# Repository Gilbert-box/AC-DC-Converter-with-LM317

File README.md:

# AC-DC Converter with LM317

This is a AC-DC Converter with LM317 voltage regulator IC.  
It converts an AC input into a stable adjustable or fixed 5V DC output using a full-wave bridge rectifier, filter capacitors, and LM317 regulator.

---

## Features

- Input: AC 12–15V (via transformer secondary)
- Output: 1.25V – 12V DC (adjustable) or 5V Fixed 
  *(depends on input voltage and load conditions)*
- Maximum Output Current: 1A (need to add heatsink)
- Built-in fuse protection on AC input

---

## How It Works

1. AC to DC Conversion
   The input AC voltage passes through a **fuse (F1)** for protection.  
   The **bridge rectifier (D1–D4)** converts AC to DC signal.

2. Input Filter 
   Two decoupling capacitors:
   - Polarized Capacitor 1000µF smooths the rectified DC.  
   - Non Polarized 100nF filter high-frequency noise input.

4. Voltage Regulation (LM317)  
   The LM317 regulates the voltage according to the equation:  

5. Output Filter
   Two decoupling capacitors:
   - Polarized Capacitor 1000µF smooths the regulator output.  
   - Non Polarized 100nF filter high-frequency noise.
    
7. Load Output 
   The regulated DC voltage is available at J2 connector pins.

---

## Design Notes

- Use a **12–18V AC transformer** capable of at least **1A output current**.  
- The LM317 requires a **heatsink** for continuous load operation.  
- Output voltage ripple depends on **C1** and load current — for lower ripple, increase C1.  
- Always ensure correct **polarity** before connecting your load.

---

## Applications

- Bench/lab adjustable DC power source  
- Battery charging experiments  
- Testing and calibration of small circuits  
- Educational demonstration of linear voltage regulation

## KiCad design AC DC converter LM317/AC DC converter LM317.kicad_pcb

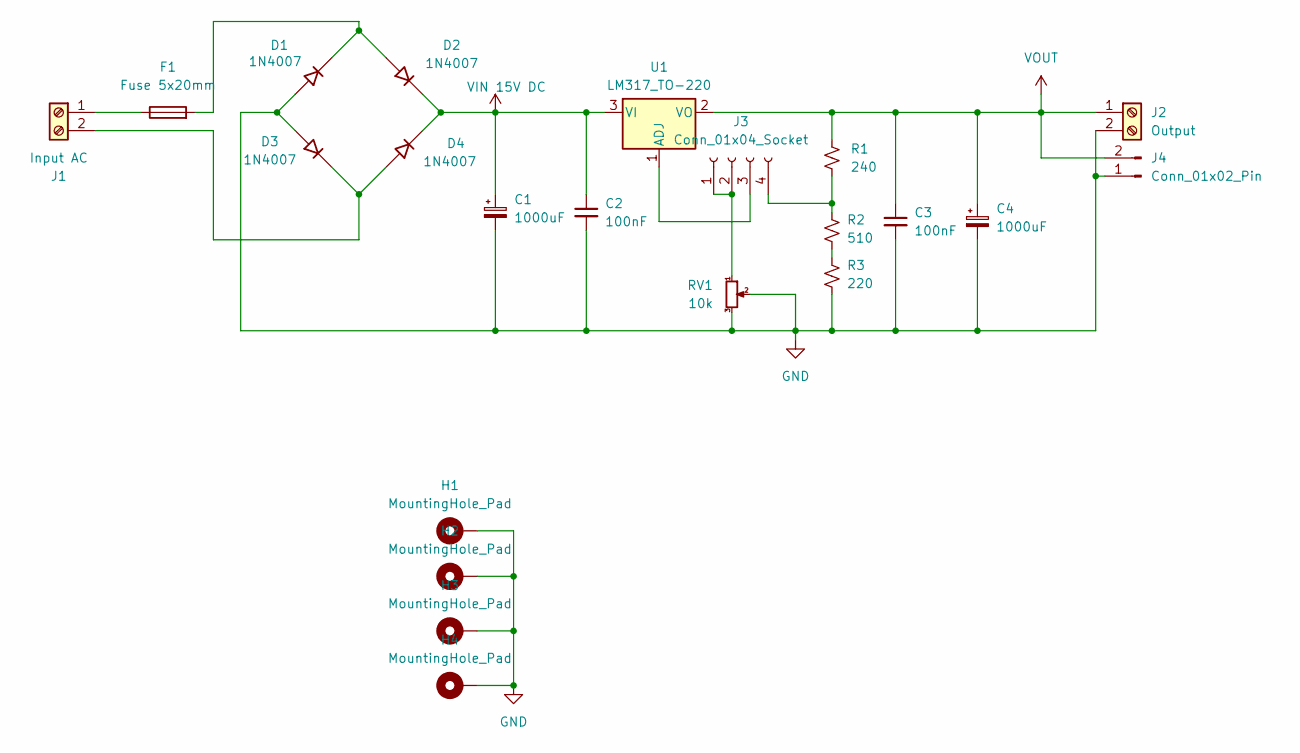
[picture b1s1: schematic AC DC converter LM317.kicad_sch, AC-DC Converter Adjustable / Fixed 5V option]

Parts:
C1, C4: 1000uF; CP_Radial_D10.0mm_P5.00mm
C2, C3: 100nF; C_Rect_L7.0mm_W2.5mm_P5.00mm
D1, D2, D3, D4: 1N4007; D_DO-41_SOD81_P10.16mm_Horizontal
F1: Fuse 5x20mm; Fuseholder_Cylinder-5x20mm_Stelvio-Kontek_PTF78_Horizontal_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
H1, H2, H3, H4: MountingHole_Pad; MountingHole_3.2mm_M3_Pad
J1: Input AC; TerminalBlock_bornier-2_P5.08mm
J2: Output; TerminalBlock_bornier-2_P5.08mm
J3: Conn_01x04_Socket; PinHeader_1x04_P2.54mm_Vertical
J4: Conn_01x02_Pin; PinHeader_1x02_P2.54mm_Vertical
R1: 240; R_Axial_DIN0207_L6.3mm_D2.5mm_P7.62mm_Horizontal
R2: 510; R_Axial_DIN0207_L6.3mm_D2.5mm_P7.62mm_Horizontal
R3: 220; R_Axial_DIN0207_L6.3mm_D2.5mm_P7.62mm_Horizontal
RV1: 10k; Potentiometer_Bourns_3296W_Vertical
U1: LM317_TO-220; TO-220-3_Vertical

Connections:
GND: C1.2, C2.2, C3.2, C4.2, D1.2 (A), D3.2 (A), H1.1, H2.1, H3.1, H4.1, J2.2, J4.1, R3.2, RV1.2, RV1.3
unnamed 1: D1.1 (K), D2.2 (A), F1.2; also elsewhere on the board
unnamed: D3.1 (K), D4.2 (A), J1.2
unnamed 3: F1.1, J1.1; also elsewhere on the board
unnamed: J3.1, J3.2, RV1.1
unnamed: J3.3, U1.1 (ADJ)
unnamed: J3.4, R1.2, R2.1
unnamed: R2.2, R3.1
VIN 15V DC: C1.1, C2.1, D2.1 (K), D4.1 (K), U1.3 (VI)
VOUT: C3.1, C4.1, J2.1, J4.2, R1.1, U1.2 (VO)

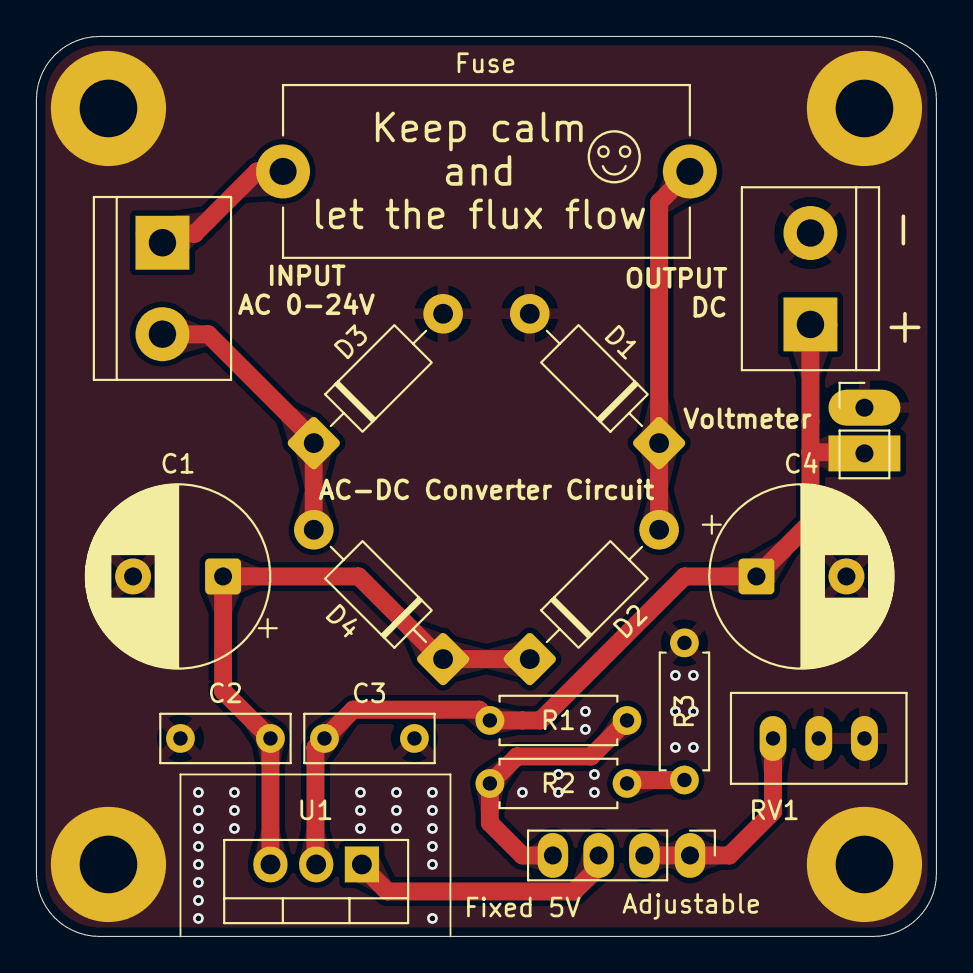
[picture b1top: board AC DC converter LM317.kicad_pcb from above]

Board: 2 copper layers, 50.0 x 50.0 mm, 22 parts (0 on the bottom side), 10 nets.

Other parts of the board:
Fuse: Fuse 5x20mm; Fuseholder_Cylinder-5x20mm_Stelvio-Kontek_PTF78_Horizontal_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

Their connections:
unnamed 1: Fuse.2; also elsewhere on the board
unnamed 3: Fuse.1; also elsewhere on the board

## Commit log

2025-09-03 Initial Commit
    Added Kicad Poject, PCB, Schematic Files
2025-09-03 Added IC Datasheet
2025-09-05 minor update
    Change R1 Value (1k to 240)
2025-10-18 Finished PCB and Schematic
2025-10-23 Added ibom html file and equation
